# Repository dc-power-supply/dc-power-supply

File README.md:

# DC Power Supply

## Description

An open source hardware (OSHW) benchtop DC power supply designed using open source tools *(WORK IN PROGRESS)*.

<br/>

## Motivation

This project started as an effort to learn the ins and outs of KiCad because
the author needed to learn how to do a hardware design for a prototype (not
related to this project). However, this side project quickly grew into a thing
of its own. It reflects the ideas and features that the author wishes for a
modern benchtop DC power supply.

Also, the world needs a modern compact **fanless** OSHW DC power supply that fits
on the table of every engineer and hacker out there. Lets design one!

Hopefully it can evolve into something which one day will be good enough to be
built and maybe even produced as a kit or product. Or it can simply serve as a
learning experience on how to do OSHW design stuff on GitHub :o)

## Design goals

 - Fanless
 - Compact size
 - Stackable housing
 - Low heat dissipation (high efficiency)
 - Low noise/ripple
 - Minimum component count
 - Simple and responsive UI
 - Beautiful mechanical design
 - Get approved by DaveCad :o)

## Features

 - 0-25V / 0-3A single DC output
 - Dimensions: ~ 60mm x 140mm x 210mm (Height x Width x Depth)
 - Low peak-to-peak voltage (max 25 mVp-p)
 - Constant current (CC)
 - Constant voltage (CV)
 - Hybrid power design
   - Preregulator: Step-down switching regulator (LT8612)
   - Regulator: Linear regulator (LT3081)
 - Precision DC output/multimeter:
   - 1 mV resolution
   - 1 mA resolution
 - AC input voltmeter:
   - 100 mV resolution
 - Large OLED display (256x64) showing:
   - Output voltage
   - Output voltage limit
   - Output current
   - Output current limit
   - Output current limit hit indicator
   - Output power
   - Input voltage (AC)
   - Regulator temperature
   - IP address
 - 4 front panel buttons:
   - On/Off
   - Voltage/Current
   - Menu
   - Lock/Unlock
 - 10/100 Mbps Ethernet port
 - 110V/220V AC input switch (automatic?)
 - Toroidal transformer
 - Replaceable fuse
 - Mains on/off switch
 - Rotary encoder with push button
 - Female banana sockets with standard spacing (19mm)
 - Built in datalogger
   - 64 MB data buffer
   - Up to 1 kHz sampling of:
     - Time
     - Voltage
     - Current
 - Master/slave feature to support higher voltage or current output
   - Link control via ethernet
   - Automatic discovery of potential slaves
   - Example configurations:
     - 25V / 6A (2 units, parallel link)
     - 50V / 3A (2 units, serial link)
     - 25V / 9A (3 units, parallel link)
     - 75V / 3A (3 units, serial link)
 - Powerful MCU (NXP LPC4337)
   - 204 MHz 32-bit Cortex-M4 core
   - 204 MHz 32-bit Cortex-M0 core
 - LXI Core support (HiSlip)
   - Support for SCPI commands to:
     - Turn on/off output
     - Get/set output voltage
     - Get/set output voltage limit
     - Get output current
     - Get/set output current limit
     - Get output power
     - Get regulator temperature
     - Get/set datalogger sampling frequency
     - Start/stop datalogger
     - Dump/clear datalogger buffer
     - Dump screenshot of front display (PNG)
 - IPv4/IPv6 support

## Documentation

 - Available [here](doc)

## Design tools

 - Schematic/PCB design
   - KiCad 4.0.7 (http://kicad.org)
   - Migrate to KiCad 5.0 when it is released

 - Mechanical design
   - Freecad 0.16.x (https://www.freecadweb.org)

## Assembly considerations

 - Minimum SMD size is 0603 to make it feasible to still hand solder

## Todo

 - Review/refine schematics
   - Add HW ID resistors
   - Add choke
   - Add protection from toroidal inrush current
   - Add AC input voltmeter
   - Add speaker
   - Add resettable fuse (PTC)
   - Add more test points
 - Review/refine PCB layout
   - Split analog and digital ground
   - Make sure tracks are wide enough
   - Minimize parasitics
   - Add more via stitching
   - Add thermal reliefs
 - Add missing KiCad 3D models
 - Rework mechanical design
   - Must be simple and beautiful
   - As compact as possible
   - Sturdy feel
 - MCU firmware
   - Create optimized GCC toolchain (http://crosstool-ng.github.io)
   - Cortex-M4:
     - Handle power control and input/output (buttons, encoder knob, USB,
       display, ethernet/LXI)
   - Cortex-M0:
     - Handle data logging
   - Implement HiSlip protocol (server)
   - Create build system files (Make or Meson)
 - Consider using MCU LPC4367JBD208 variant
   - Adds LCD controller
   - Adds QEI (Quadrature Encoder Interface, for better rotary encoder control)
 - Implement HiSlip protocol (client) in liblxi (https://lxi.github.io)
 - Add missing documentation
 - Create BOM
 - Cost reduction
 - Build a prototype for testing

## Releases

 - Version 0.1 - First release (alpha)

## Milestones

Suggested milestones:

 - Version 1.0 - First stable release (basic features working)
 - Version 2.0 - Feature release (wifi, remote sensing)
 - Version 3.0 - Feature release (2 port LAN switch, automatic power link cable, mains inlet/outlet)

## How to contribute?

This project is fully open source - anyone who wants to contribute is welcome
to get involved.

To get started, simply clone (use 'git clone --recurse-submodules') this
repository and start making your changes.  Once done, do a pull request to push
your changes upstream. Any issues (bugs, suggestions, etc.) can be reported
and/or discussed via the GitHub issue tracker. There is also a GitHub wiki
available for editing. It's the GitHub way!

**Note**: Please take care to always use the latest version of the design tools
to avoid running into compatibility issues.

**Note**: Please take care to try only push incremental changes to avoid big
bang situations.

## License

<br />This work
is licensed under a <a rel="license"
href="http://creativecommons.org/licenses/by-sa/4.0/">Creative Commons
Attribution-ShareAlike 4.0 International License</a>.

With exception of the firmware which will be released under a BSD-3 license.

##

<br/>
<br/>

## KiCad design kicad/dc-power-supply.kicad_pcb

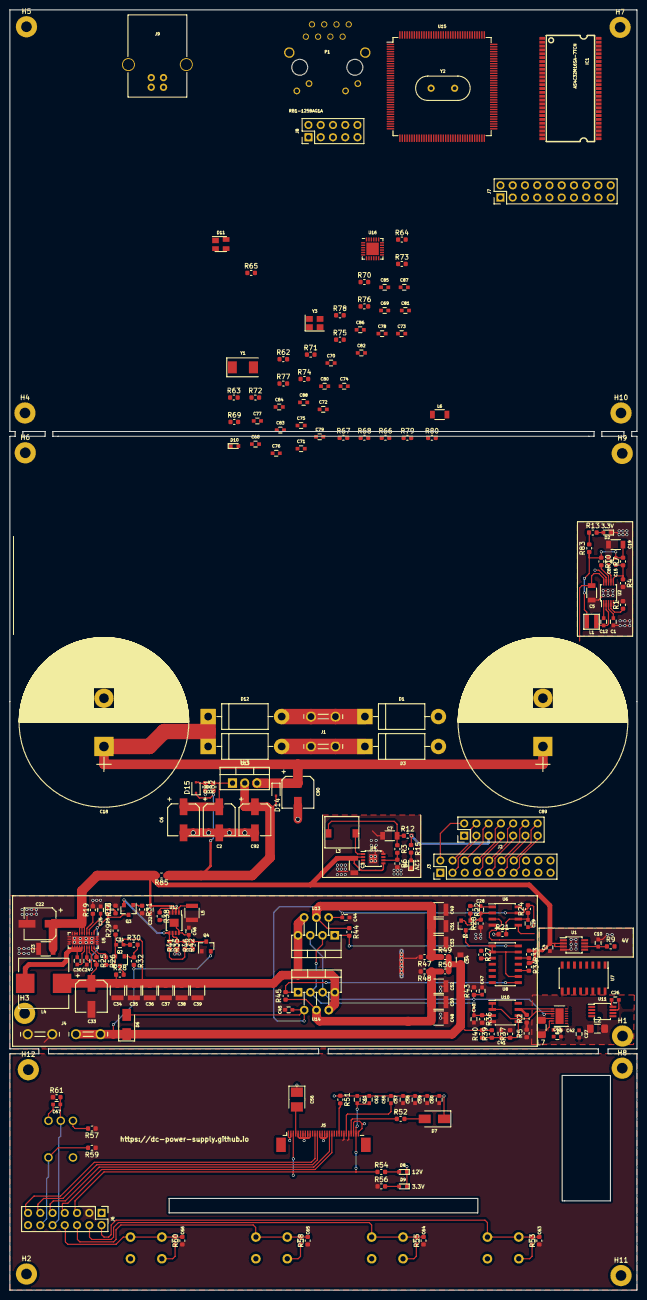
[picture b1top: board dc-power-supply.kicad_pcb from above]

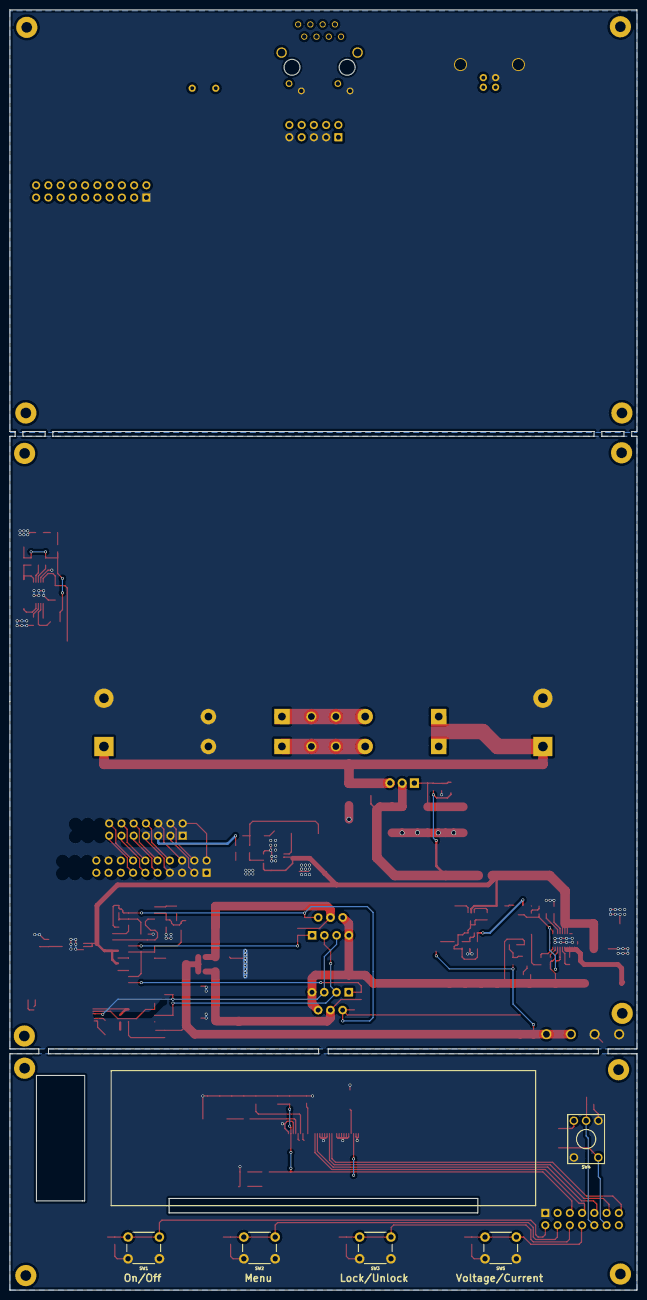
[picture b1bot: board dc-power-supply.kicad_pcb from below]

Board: 2 copper layers, 130.0 x 265.4 mm, 234 parts (5 on the bottom side), 197 nets.

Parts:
C1: 1μF; C_0603
C2, C6, C90: 10uF; CP_Elec_6.3x5.3
C3: 1μF; C_1206
C4, C25, C30, C57, C59, C61, C63, C64, C65, C66, C67, C76, C81, C82: 0.1uF; C_0603
C5: 4.7μF; C_1206
C7: 10uF; C_1206
C8, C44, C45, C47: 10nF; C_0603
C10, C24, C26, C27, C55, C74, C78: 1uF; C_0603
C12, C43: 0.1μF; C_0603
C15, C84, C85, C86, C87: 10pF; C_0603
C18, C89: 12mF; CP_Radial_D35.0mm_P10.00mm_SnapIn
C19: 22μF; C_1206
C22, C92: 22uF; CP_Elec_6.3x7.7
C23, C34, C35, C36, C37, C38, C39, C48, C49, C50, C51, C52, C53: 10uF; C_1210
C28, C29, C31: 1nF; C_0603
C32, C62, C75, C80: 10uF; C_0603
C33: 100uF; CP_Elec_6.3x7.7
C40, C41: 100nF; C_0603
C42, C46: 10μF; C_0603
C54: 1uF; C_0805
C56: 4.7uF; CP_Tantalum_Case-B_EIA-3528-21_Reflow
C58, C60, C83: 4.7uF; C_0603
C68, C69: 18pF; C_0603
C70, C71, C72, C73: 27pF; C_0603
C77: 470pF; C_0603
C79: 0.01uF; C_0603
C88: 22pF; C_0603
D1, D3, D12, D13: MUR420; D_DO-201AD_P15.24mm_Horizontal
D2, D4, D8, D9, D10: Green; LED_0603
D5: Red; LED_0603
D6: B140-13-F; D_SMA
D7: <=1.4V,0.5W; D_SMA
D11: ESD PROTECTION; SOT-143
D14, D15: BAT54; D_SOD-323F
H1, H2, H3, H4, H5, H6, H7, H8, H9, H10, H11, H12: MountingHole; MountingHole_2.2mm_M2_Pad
IC1: AS4C32M16SA-7TCN; TSOP-54
J1, J4: 2 Pin Terminal; 2_tab_250
J2, J6: 14 Pin Connector; Pin_Header_Straight_2x07_Pitch2.54mm
J3, J7: 20 Pin Connector; Pin_Header_Straight_2x10_Pitch2.54mm
J5: 30 Pins 0.50 mm Pitch ZIF Connector; Molex_Plug_1x30_Pitch0.5mm
J8: 10 Pin Connector; Pin_Header_Straight_2x05_Pitch2.54mm
J9: USB_B
L1: 2.2uH; XFL3012
L2, L7: Ferrite_Bead_Small; R_1206_3216Metric_Pad1.42x1.75mm_HandSolder
L3: 100uH; DQ6545
L4: 5.5uH; Inductor_Wurth_HCI-1050
L5: 470uH; R_1210
L6: 10; C_1206
P1: RB1-125BAG1A; WIZNET_RB1-125BAG1A
Q1: BC847; SOT-23
Q2, Q3: MMBT3906-7-F; SOT-23
Q4: FMMT493TA; SOT-23
R1: 18.2k; R_0603_1608Metric
R2, R10, R30, R32: 100k; R_0603_1608Metric
R3, R7, R67: 1M; R_0603_1608Metric
R4: 309k; R_0603_1608Metric
R5, R22, R26, R28, R31, R37: 1k; R_0603_1608Metric
R6: 71.5k; R_0603_1608Metric
R9, R12, R79, R80, R83, R85: 0; R_0603_1608Metric
R13, R56, R63, R71: 2.2k; R_0603_1608Metric
R15, R54: 8.2k; R_0603_1608Metric
R16, R46: 549; R_0603_1608Metric
R19: 60.4k; R_0603_1608Metric
R20: 30.9k; R_0603_1608Metric
R21, R35, R47, R48, R53, R55, R57, R58, R59, R60, R61, R62, R64, R65: 10k; R_0603_1608Metric
R24: 52.3k; R_0603_1608Metric
R25, R29, R36, R43: 4.99k; R_0603_1608Metric
R27, R33, R34: 6k; R_0603_1608Metric
R38: 806k; R_0603_1608Metric
R39: 9.09k; R_0603_1608Metric
R40: 909k; R_0603_1608Metric
R41: 1.47M; R_0603_1608Metric
R42: 280k; R_0603_1608Metric
R44, R45: 402; R_0603_1608Metric
R49, R50: 0.010; R_0603_1608Metric
R51: 680k; R_0603_1608Metric
R52: 50; R_0603_1608Metric
R66: 33; R_0603_1608Metric
R68: 1.5k; R_0603_1608Metric
R69, R72: 12.1k; R_0603_1608Metric
R70: 470; R_0603_1608Metric
R73, R74, R75, R76: 49.9; R_0603_1608Metric
R77, R78: 220; R_0603_1608Metric
R81: 4.75k; R_0603_1608Metric
R82: 200; R_0603_1608Metric
SW1: On/Off; SW_PUSH_6mm
SW2: Menu; SW_PUSH_6mm
SW3: Lock/Unlock; SW_PUSH_6mm
SW4: 318-ENC130175F-12PS; KSA_Tactile_SPST
SW5: Voltage/Amp; SW_PUSH_6mm
U1: LT6657; MSOP-8_3x3mm_Pitch0.65mm
U2: LT8607; MSOP-10_3x3mm_Pitch0.5mm
U3: LM338T; TO-220-3_Vertical
U4: LTC3631; MSOP-8-1EP_3x3mm_Pitch0.65mm
U5: LT8612EUDE; QFN-28-1EP_3x6mm_Pitch0.5mm
U6, U10: LT1013DS; SOIC-8_3.9x4.9mm_Pitch1.27mm
U7: ADuM262N; SOIC-16_3.9x9.9mm_Pitch1.27mm
U8: 320S14; SOIC-14_3.9x8.7mm_Pitch1.27mm
U9: LTC2486; DFN-14-1EP_3x4mm_Pitch0.5mm
U11: LTC2602; MSOP-8_3x3mm_Pitch0.65mm
U12: LTC3632EDD; MSOP-8-1EP_3x3mm_Pitch0.65mm
U13, U14: LT3081ER; TO-220-7_Vertical_StaggeredType2
U15: LPC4337JBD144; LQFP-144_20x20mm_Pitch0.5mm
U16: LAN8720A; QFN-24-1EP_4x4mm_Pitch0.5mm
Y1: 32.768 kHz; Crystal_SMD_0603-2pin_6.0x3.5mm
Y2: 12 MHz; Crystal_HC49-U_Vertical
Y3: 25MHz; Crystal_SMD_3225-4pin_3.2x2.5mm

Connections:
+3V3: C42.1, C43.1, C57.1, C58.1, C59.1, C60.1, C75.1, C76.1, C79.1, C80.1, C83.1, C88.1, IC1.1, IC1.3, IC1.9, IC1.14, IC1.27, IC1.43, IC1.49, J2.3, J3.3, J5.24, J5.26, J6.3, J7.3, J8.1, L2.2, L6.2, L7.1, P1.R3, R13.1, R53.1, R55.1, R56.1, R57.1, R58.1, R59.1, R60.1, R61.1, R62.1, R63.1, R64.1, R65.1, R68.1, R80.2, R83.2, U7.1, U7.16, U9.12, U11.6, U15.5, U15.25, U15.36, U15.41, U15.59, U15.71, U15.77, U15.94, U15.107, U15.111, U15.131, U15.141, U16.9
+12V: J2.5, R12.2, R15.1, U10.8
+30V: C3.1, C4.1, C5.1, C22.1, C23.1, C32.1, R27.1, R33.1, R34.1, R85.2, U1.2, U1.3, U2.10, U4.2, U4.5, U5.5, U5.6, U5.7, U6.8, U12.2
/power_supply_board/AC+: D1.1, D12.2, J1.1
/power_supply_board/AC-: D3.1, D13.2, J1.2
/power_supply_board/VOUT+: C54.1, D6.1, J4.2, Q4.2, R32.2, R39.2, R40.2, R49.2, R50.2
EMC_A0: IC1.23, U15.102
EMC_A1: IC1.24, U15.104
EMC_A2: IC1.25, U15.105
EMC_A3: IC1.26, U15.106
EMC_A4: IC1.29, U15.108
EMC_A5: IC1.30, U15.38
EMC_A6: IC1.31, U15.42
EMC_A7: IC1.32, U15.43
EMC_A8: IC1.33, U15.98
EMC_A9: IC1.34, U15.96
EMC_A10: IC1.22, U15.95
EMC_A11: IC1.35, U15.84
EMC_A12: IC1.36, U15.81
EMC_CKEOUT0: IC1.37, U15.101
EMC_CLK0: IC1.38, U15.45
EMC_D0: IC1.2, U15.50
EMC_D1: IC1.4, U15.51
EMC_D2: IC1.5, U15.52
EMC_D3: IC1.7, U15.53
EMC_D4: IC1.8, U15.55
EMC_D5: IC1.10, U15.56
EMC_D6: IC1.11, U15.60
EMC_D7: IC1.13, U15.61
EMC_D8: IC1.42, U15.57
EMC_D9: IC1.44, U15.58
EMC_D10: IC1.45, U15.63
EMC_D11: IC1.47, U15.65
EMC_D12: IC1.48, U15.37
EMC_D13: IC1.50, U15.39
EMC_D14: IC1.51, U15.46
EMC_D15: IC1.53, U15.54
EMC_DQMOUT0: IC1.15, U15.103
EMC_DQMOUT1: IC1.39, U15.100
ENET_CRS_DV: U15.64, U16.11
ENET_MDC: U15.75, U16.13
ENET_MDIO: R68.2, U15.66, U16.12
ENET_REF_CLK: R66.2, U15.68
ENET_RXD0: U15.62, U16.8
ENET_RXD1: U15.32, U16.7
ENET_TXD0: U15.67, U16.17
ENET_TXD1: U15.70, U16.18
ENET_TX_EN: U15.34, U16.16
GND: C1.2, C2.2, C3.2, C4.2, C5.2, C6.2, C7.2, C8.2, C10.2, C18.2, C19.2, C22.2, C23.2, C24.2, C25.2, C26.2, C27.2, C32.2, C33.2, C34.2, C35.2, C36.2, C37.2, C38.2, C39.2, C40.2, C41.2, C42.2, C43.2, C44.2, C45.2, C46.1, C47.2, C48.2, C49.2, C50.2, C51.2, C52.2, C53.2, C54.2, C55.2, C56.1, C57.2, C58.2, C59.2, C60.2, C61.1, C62.1, C63.2, C64.2, C65.2, C66.2, C67.2, C68.2, C69.1, C70.2, C71.1, C72.1, C73.2, C74.1, C75.2, C76.2, C77.2, C78.2, C79.2, C80.2, C81.1, C82.1, C83.2, C84.1, C85.1, C86.1, C87.1, C88.2, C89.2, C90.2, C92.2, D1.2, D2.1, D3.2, D4.1, D7.1, D8.1, D9.1, D10.1, D11.1, IC1.6, IC1.12, IC1.28, IC1.41, IC1.46, IC1.52, IC1.54, J2.1, J3.1, J4.1, J5.1, J5.2, J5.5, J5.6, J5.7, J5.8, J5.9, J5.10, J5.14, J5.15, J5.16, J5.17, J5.28, J5.30, J6.1, J7.1, J8.3, J8.5, J8.9, J9.4, J9.5, L5.2, P1.L2, P1.L4, Q4.1, R1.2, R4.2, R5.1, R6.2, R16.2, R19.2, R20.1, R21.1, R29.2, R31.2, R36.2, R37.2, R41.1, R43.2, R47.2, R48.2, R51.1, R69.2, R71.1, R72.2, R79.2, R82.2, SW1.1, SW2.1, SW3.1, SW4.2, SW4.5, SW5.1, U1.4, U2.9, U4.8, U4.9, U5.8, U5.9, U5.10, U5.11, U5.12, U5.13, U5.14, U5.25, U5.26, U5.27, U5.28, U5.29, U6.4, U7.8, U7.9, U9.1, U9.6, U9.7, U9.14, U9.15, U10.4, U11.7, U15.4, U15.40, U15.76, U15.109, U15.135, U16.25, Y3.2, Y3.4
IMON: U9.9, U10.1, U10.2
ISET: C26.1, U6.3, U11.8
JTAG_TCK/SWDCLK: J8.4, R64.2, U15.27
JTAG_TDI: J8.8, U15.26
JTAG_TDO/SWO: J8.6, R65.2, U15.31
JTAG_TMS/SWDIO: J8.2, U15.30
LOCK/UNLOCK_BUTTON: J7.6, U15.115
MENU_BUTTON: J7.4, U15.113
NET_RESET: U15.74, U16.15
unnamed: C1.1, U2.3
unnamed: C2.1, C6.1, D15.2, R81.2, R82.1, U3.1
unnamed: C7.1, L3.2, R3.1, R12.1
unnamed: C8.1, U2.7
unnamed: C10.1, R9.1, U1.6
unnamed: C12.1, U2.1
unnamed: C12.2, L1.1, U2.2
unnamed: C15.1, R4.1, R7.1, U2.6
unnamed: C15.2, C19.1, L1.2, R7.2, R10.1, R83.1
unnamed: C18.1, C89.1, C90.1, D12.1, D13.1, D14.1, U3.3
unnamed: C24.1, D5.2, Q3.3, U5.1, U5.21
unnamed: C25.1, U5.3
unnamed: C28.1, R22.1, U6.1
unnamed: C28.2, Q1.2, R20.2, U6.2
unnamed: C29.1, C44.1, C45.1, D6.2, R24.2, U6.7, U13.2, U14.2
unnamed: C29.2, R21.2, R24.1, U6.6
unnamed: C30.1, U5.20
unnamed: C30.2, L4.1, U5.15, U5.16, U5.17, U5.18, U5.19
unnamed: C31.1, Q2.2, R26.2, R29.1
unnamed: C31.2, C33.1, C34.1, C35.1, C36.1, C37.1, C38.1, C39.1, L4.2, R25.2, R28.1, R30.1, U5.22, U13.6, U13.7, U14.6, U14.7
unnamed: C40.1, R36.1, U10.3, U13.3, U14.3
unnamed: C41.1, R37.1, R39.1, R40.1, U10.5
unnamed: C46.2, R35.2, R38.2, R42.2, R46.1, U12.8, U12.9
unnamed: C48.1, C50.1, C52.1, R45.1, R48.1, R50.1, U14.4
unnamed: C49.1, C51.1, C53.1, R44.1, R47.1, R49.1, U13.4
unnamed: C55.1, J5.25
unnamed: C56.2, J5.4
unnamed: C61.2, C62.2, J5.3, J5.29, J6.5, R54.1
unnamed: C63.1, J6.2, R53.2, SW1.2
unnamed: C64.1, J6.4, R55.2, SW2.2
unnamed: C65.1, J6.6, R58.2, SW3.2
unnamed: C66.1, J6.8, R60.2, SW5.2
unnamed: C67.1, J6.10, R61.2, SW4.4
unnamed: C68.1, U15.125, Y1.1
unnamed: C69.2, U15.126, Y1.2
unnamed: C70.1, U15.13, Y2.1
unnamed: C71.2, U15.12, Y2.2
unnamed: C72.2, R67.2, U16.5, Y3.1
unnamed: C73.1, R67.1, U16.4, Y3.3
unnamed: C74.2, D11.4, J9.1, R70.1, R71.2
unnamed: C77.1, C78.1, U16.6
unnamed: C81.2, C82.2, L6.1, R73.1, R74.1, R75.1, R76.1, U16.1, U16.19
unnamed: C84.2, P1.R8, R76.2, U16.22
unnamed: C85.2, P1.R7, R75.2, U16.23
unnamed: C86.2, P1.R2, R74.2, U16.20
unnamed: C87.2, P1.R1, R73.2, U16.21
unnamed: C92.1, D14.2, D15.1, R81.1, R85.1, U3.2
unnamed: D2.2, R13.2
unnamed: D4.2, R15.2
unnamed: D5.1, R16.1
unnamed: D7.2, R52.2
unnamed: D8.2, R54.2
unnamed: D9.2, R56.2
unnamed: D10.2, R63.2
unnamed: J2.2, J3.2
unnamed: J2.4, J3.4
unnamed: J2.6, J3.6
unnamed: J2.7, J3.7
unnamed: J2.8, J3.8
unnamed: J2.9, J3.9
unnamed: J2.10, J3.10
unnamed: J2.11, J3.11
unnamed: J2.12, J3.12
unnamed: J2.13, J3.13
unnamed: J2.14, J3.14
unnamed: J5.12, J6.13
unnamed: J5.13, J6.11
unnamed: J5.18, J6.9
unnamed: J5.19, J6.7
unnamed: J5.22, R51.2
unnamed: J5.27, R52.1
unnamed: J6.12, R59.2, SW4.1
unnamed: J6.14, R57.2, SW4.3
unnamed: L2.1, U11.4
unnamed: L3.1, U4.1
unnamed: L5.1, U12.1
unnamed: L7.2, U9.13
unnamed: P1.L1, R77.2
unnamed: P1.L3, R78.2
unnamed: Q1.1, R22.2
unnamed: Q1.3, U8.1, U8.2, U8.9, U8.13
unnamed: Q2.1, R30.2, R32.1
unnamed: Q2.3, R28.2
unnamed: Q3.1, R31.1
unnamed: Q3.2, R35.1, U12.5
unnamed: Q4.3, R46.2
unnamed: R1.1, U2.4
unnamed: R2.1, R5.2, U10.6
unnamed: R3.2, R6.1, U4.6
unnamed: R10.2, U2.8
unnamed: R19.1, U5.4
unnamed: R25.1, U5.23
unnamed: R26.1, U5.24
unnamed: R27.2, U8.3
unnamed: R33.2, U8.12
unnamed: R34.2, U8.10
unnamed: R38.1, U12.3
unnamed: R41.2, R42.1, U12.6
unnamed: R44.2, U8.14, U13.1
unnamed: R45.2, U8.8, U14.1
unnamed: R62.2, U15.28
unnamed: R66.1, U16.14
unnamed: R72.1, U16.24
unnamed: R77.1, U16.3
unnamed: R78.1, U16.2
unnamed: U7.10, U9.5
unnamed: U7.13, U9.4
unnamed: U7.12, U11.1
unnamed: U7.14, U9.3, U11.2
unnamed: U7.15, U9.2, U11.3
ON/OFF_BUTTON: J7.2, U15.110
PSU_ON/OFF: J3.16, J7.16, U7.6, U7.11, U15.78
ROTARY_A: J7.12, U15.133
ROTARY_B: J7.14, U15.134
ROTARY_BUTTON: J7.10, U15.132
SSP0_MISO: J7.9, U15.123
SSP0_MOSI: J7.13, U15.124
SSP0_SCK: J7.11, U15.118
SSP0_SSEL: J7.7, U15.122
SSP1_MISO: J3.17, J7.17, U7.7, U15.44
SSP1_MOSI: J3.19, J7.19, U7.2, U15.47
SSP1_SCK: J3.15, J7.15, U7.3, U15.120
SSP1_SSEL_ADC: J3.18, J7.18, U7.4, U15.114
SSP1_SSEL_DAC: J3.20, J7.20, U7.5, U15.116
TEMP: C47.1, R43.1, U9.10, U13.5, U14.5
USB0_DM: D11.3, J9.2, U15.20
USB0_DP: D11.2, J9.3, U15.18
USB0_RREF: R69.1, U15.24
USB0_VBUS: R70.2, U15.21
USB0_VDDA: R80.1, U15.16, U15.17
USB0_VSSA_REF: R79.1, U15.19, U15.23
VOLTAGE/AMP_BUTTON: J7.8, U15.117
VOUT: R2.2, U9.8, U10.7
VSET: C27.1, U6.5, U11.5
~EMC_CAS: IC1.17, U15.80
~EMC_CS0: IC1.19, U15.48
~EMC_RAS: IC1.18, U15.82
~EMC_WE: IC1.16, U15.49
~RESET: J8.10, U15.128

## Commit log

2017-11-27 Import files
2017-11-27 Add WIP note
2020-10-04 Made some major and minor design changes
    * Decided on using a 40VAC transformer instead of a toroid. This freed up a lot space for the uC board.
    * Switched to a LM338T regulator from TI instead of the more expensive LT part
    - Added protection diode
    - Changed values of feedback resistors to account for minimum load current
    * Added a Ferrite bead to +3v3 Rail and used it for reference for the ADC and the DAC. This fixes the Vref > Vcc issue. Don't need the precision 4V supply anymore
    * Changed U10B to a Non-inverting Amp with a G = 1000. This gives us a higher voltage to work with. Was originally 0.6mV at max output current.
2021-11-09 Update README.md
    https://forum.kicad.info/t/warning-avoid-all-links-to-kicad-pcb-org-use-kicad-org/31521
